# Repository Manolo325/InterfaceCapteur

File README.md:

# InterfaceCapteur
Projet L3-EEA, conception et réalisation d'un circuit analogique pour retourner sur commande la distance par rapport à un obstacle avec une tension.

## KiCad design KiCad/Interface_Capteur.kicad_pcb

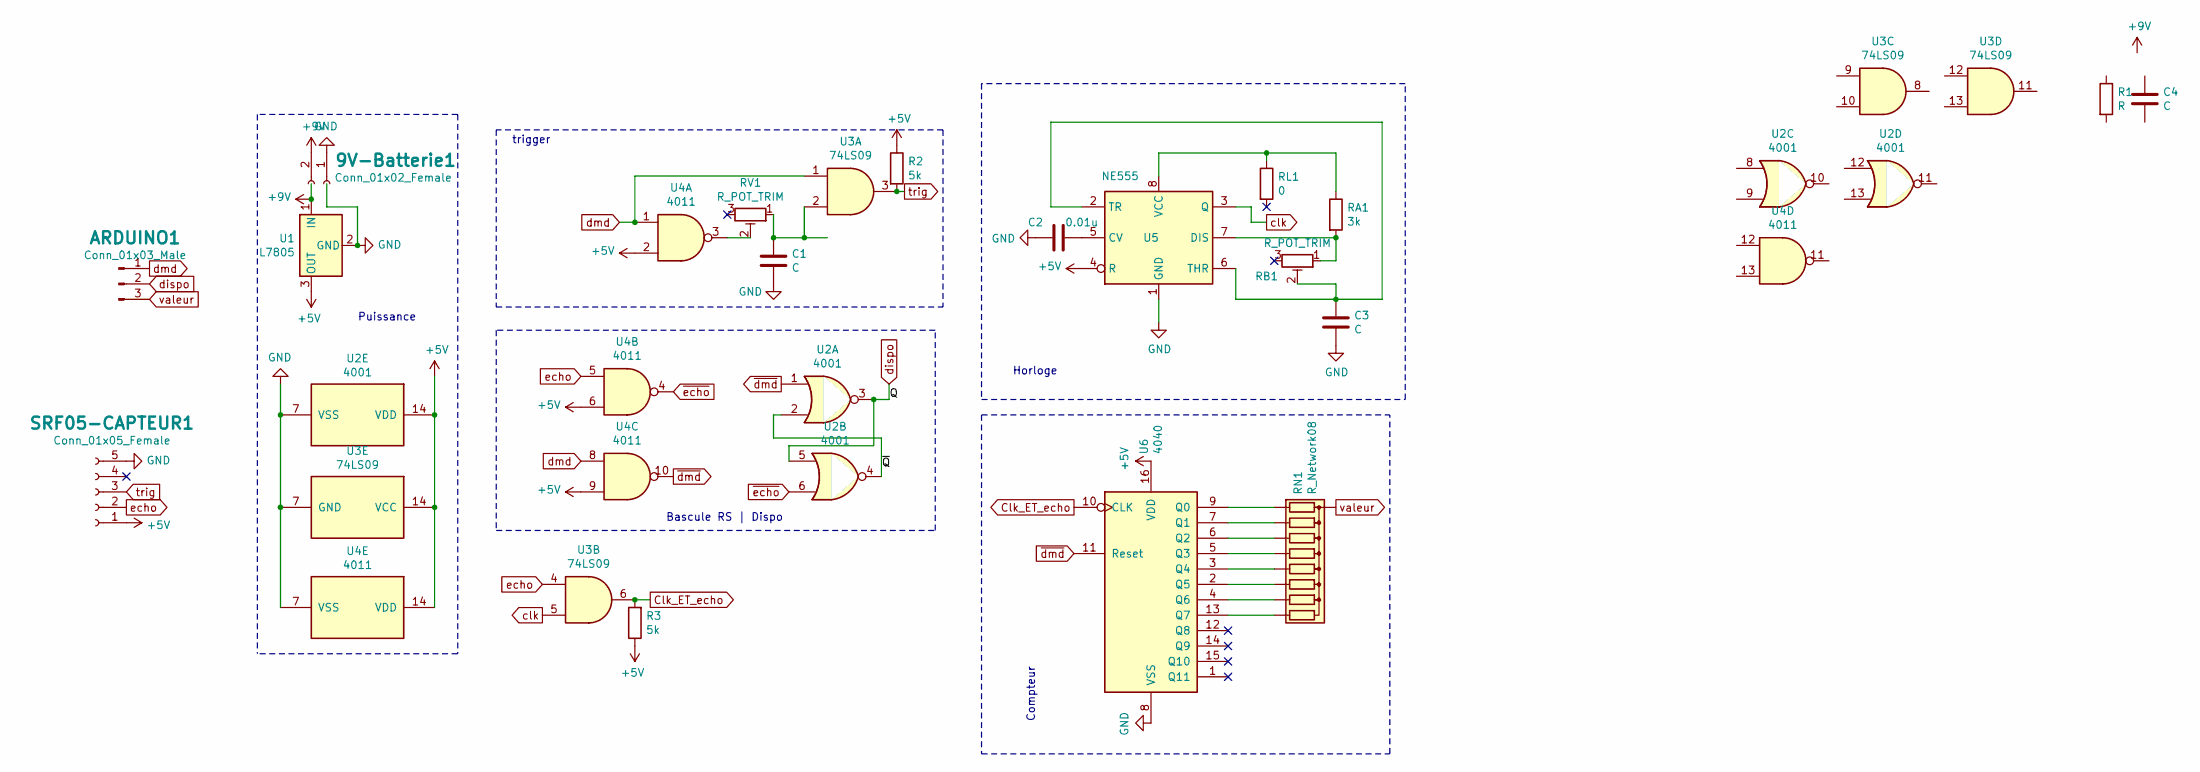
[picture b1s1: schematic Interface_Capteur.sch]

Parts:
9V-Batterie1: Conn_01x02_Female; BarrelJack_CUI_PJ-063AH_Horizontal
ARDUINO1: Conn_01x03_Male; PinHeader_1x03_P2.54mm_Horizontal
C1, C3, C4: C; C_Disc_D3.8mm_W2.6mm_P2.50mm
C2: 0.01u; C_Disc_D3.8mm_W2.6mm_P2.50mm
R1: R; R_Axial_DIN0204_L3.6mm_D1.6mm_P1.90mm_Vertical
R2, R3: 5k; R_Axial_DIN0204_L3.6mm_D1.6mm_P1.90mm_Vertical
RA1: 3k; R_Axial_DIN0204_L3.6mm_D1.6mm_P1.90mm_Vertical
RB1: R_POT_TRIM; Potentiometer_Bourns_3339P_Vertical
RL1: 0; R_Axial_DIN0204_L3.6mm_D1.6mm_P1.90mm_Vertical
RN1: R_Network08; R_Array_SIP9
RV1: R_POT_TRIM; Potentiometer_Bourns_3339P_Vertical
SRF05-CAPTEUR1: Conn_01x05_Female; PhoenixContact_MSTBA_2,5_5-G-5,08_1x05_P5.08mm_Horizontal
U1: L7805; TO-220-3_Horizontal_TabDown
U2: 4001; DIP-14_W7.62mm_Socket_LongPads
U3: 74LS09; DIP-14_W7.62mm_Socket_LongPads
U4: 4011; DIP-14_W7.62mm_Socket_LongPads
U5: NE555; DIP-8_W7.62mm_LongPads
U6: 4040; DIP-16_W7.62mm_Socket_LongPads

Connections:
+5V: R2.1, R3.1, SRF05-CAPTEUR1.1, U1.3 (OUT), U2.14 (VDD), U3.14 (VCC), U4.2, U4.6, U4.9, U4.14 (VDD), U5.4 (R), U6.16 (VDD)
+9V: 9V-Batterie1.2, U1.1 (IN)
/~Q: U2.2, U2.4
Clk_ET_echo: R3.2, U3.6, U6.10 (CLK)
GND: 9V-Batterie1.1, C1.2, C2.2, C3.2, SRF05-CAPTEUR1.5, U1.2 (GND), U2.7 (VSS), U3.7 (GND), U4.7 (VSS), U5.1 (GND), U6.8 (VSS)
unnamed: C1.1, RV1.1, U3.2
unnamed: C2.1, U5.5 (CV)
unnamed: C3.1, RB1.2, U5.2 (TR), U5.6 (THR)
unnamed: RA1.1, RL1.1, U5.8 (VCC)
unnamed: RA1.2, RB1.1, U5.7 (DIS)
unnamed: RN1.2 (R1), U6.9 (Q0)
unnamed: RN1.3 (R2), U6.7 (Q1)
unnamed: RN1.4 (R3), U6.6 (Q2)
unnamed: RN1.5 (R4), U6.5 (Q3)
unnamed: RN1.6 (R5), U6.3 (Q4)
unnamed: RN1.7 (R6), U6.2 (Q5)
unnamed: RN1.8 (R7), U6.4 (Q6)
unnamed: RN1.9 (R8), U6.13 (Q7)
unnamed: RV1.2, U4.3
clk: U3.5, U5.3 (Q)
dispo: ARDUINO1.2, U2.3, U2.5
dmd: ARDUINO1.1, U3.1, U4.1, U4.8
echo: SRF05-CAPTEUR1.2, U3.4, U4.5
trig: R2.2, SRF05-CAPTEUR1.3, U3.3
valeur: ARDUINO1.3, RN1.1 (common)
~dmd: U2.1, U4.10, U6.11 (Reset)
~echo: U2.6, U4.4

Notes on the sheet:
trigger
Puissance
Horloge
Compteur
Bascule RS | Dispo

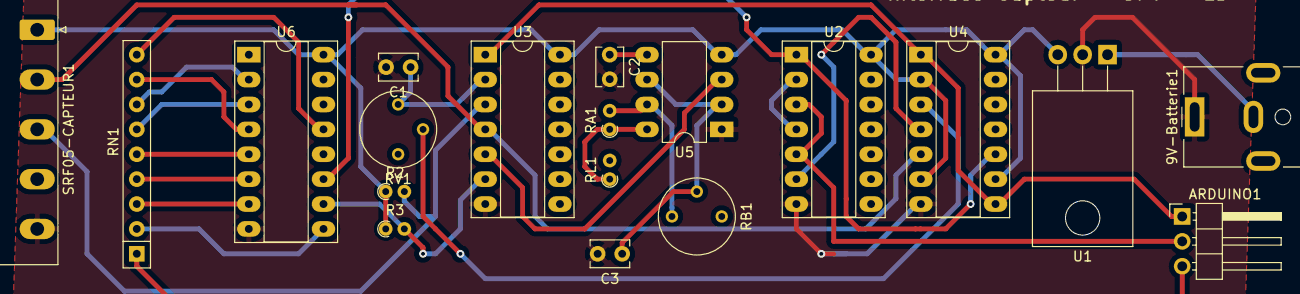
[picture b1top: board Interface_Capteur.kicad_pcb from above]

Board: 2 copper layers, 19 parts (0 on the bottom side), 27 nets.

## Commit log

2019-02-07 Separation des parties et objectifs
2019-02-07 Create empty
2019-02-07 LaTex
2019-02-07 Liste des composants
    Liste des composants et des datasheet acquises ou à trouver
2019-02-07 Update liste des composants
2019-02-07 SRF04 Data Sheet
2019-02-07 NE555 DataSheet
2019-02-07 Create LTspice's ReadMe
2019-02-08 Create toDelete
2019-02-08 une librairie additionnelle
    Op Amps LM741 ... librairie de " " . J'ai oublié la source.
2019-02-08 FirstdrawIOgraph
2019-02-08 (Git) Projet Transversal Elelctronique : Schéma Bloc
2019-02-08 Rename Untitled Diagram.xml to Projet_Transversal_Elelctronique-Schéma_Bloc.xml
2019-02-08 Added (Git) Projet Transversal Elelctronique : Schéma Bloc
2019-02-08 doublon
2019-02-08 PDF version ShémaBloc
2019-02-12 Change names and correct errors
2019-02-25 toutes les datasheets
    Avec ça toutes les datasheet sont présentes
2019-03-01 remise de shem
2019-04-11 mise à jour
2019-04-24 init Kicad folder
2019-04-24 Kicad_Files
